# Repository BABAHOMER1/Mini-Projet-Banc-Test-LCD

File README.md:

# Banc d'essais pour écran LCD

## Présentation du projet

Ce projet a pour objectif de réaliser un banc d'essais permettant de tester des écrans LCD.

Les écrans proviennent d'un lot donné à l'établissement et leur fonctionnement n'est pas garanti.
Le banc d'essais permet donc de vérifier rapidement si un écran fonctionne correctement.

## Objectifs

- [ ] Tester l'affichage de caractères
- [ ] Permettre une connexion simple de l'écran au banc d'essais
- [ ] Réaliser une procédure de test complète et efficace
- [ ] Ajouter un potentiomètre pour le réglage du contraste
- [ ] Créer le symbole et l'empreinte de l'écran LCD
- [ ] Réaliser le schéma électronique
- [ ] Ajouter des points de test
- [ ] Réaliser le PCB

## Programmation

- [ ] Le programme de test est développé en langage C avec SimulIDE.
- [ ] La bibliothèque LiquidCrystal est utilisée pour contrôler l'écran LCD.
- [ ] L'écran fonctionne en mode 4 bits.
- [ ] Le programme de test se lance lorsque l'on appuie sur le bouton.
  
## Procédure de test

La procédure permet de vérifier progressivement le fonctionnement de l'écran

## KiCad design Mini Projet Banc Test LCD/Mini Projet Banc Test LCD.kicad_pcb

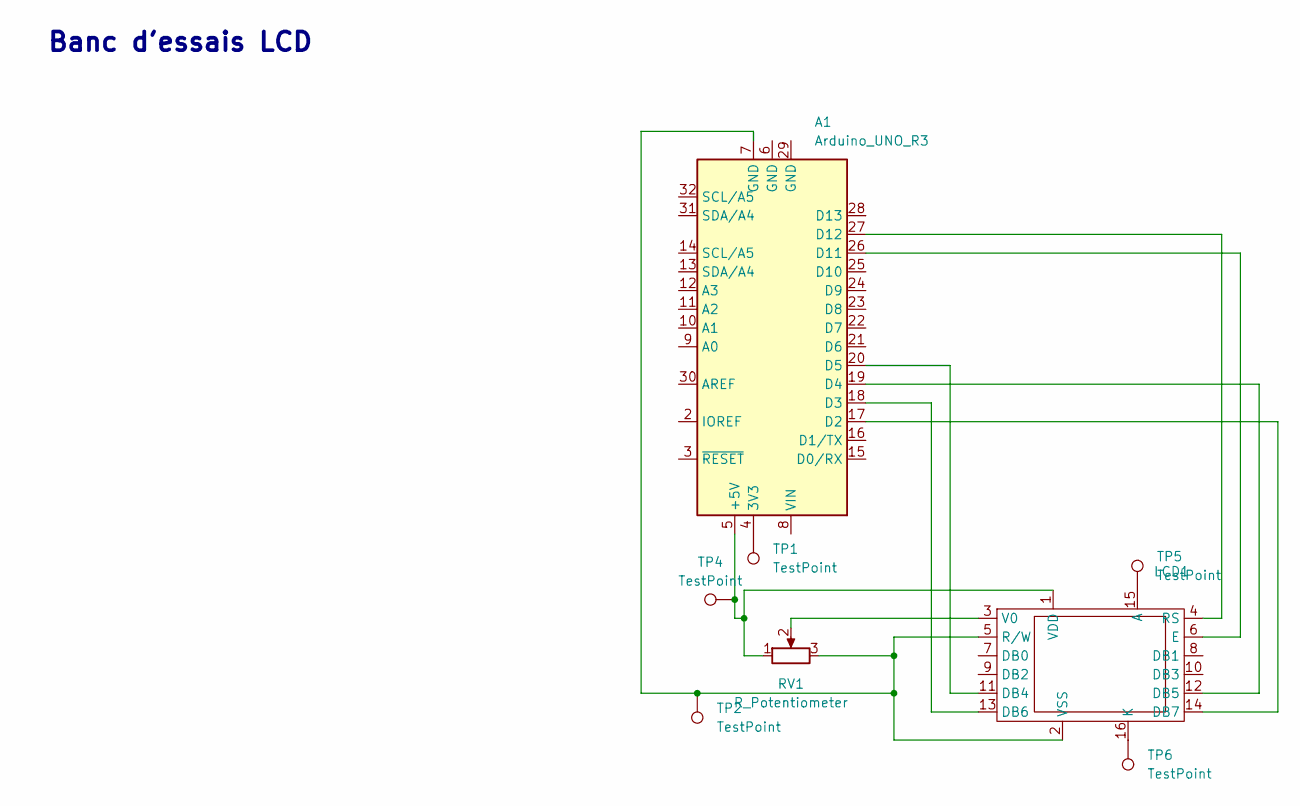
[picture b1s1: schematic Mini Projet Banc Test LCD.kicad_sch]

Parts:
A1: Arduino_UNO_R3
LCD1: LCD hitachi
RV1: R_Potentiometer; Potentiometer_ACP_CA6-H2,5_Horizontal
TP1, TP2, TP4, TP5, TP6: TestPoint; Pin_D0.7mm_L6.5mm_W1.8mm_FlatFork

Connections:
unnamed: A1.4 (3V3), TP1.1
unnamed: A1.5 (+5V), LCD1.1 (VDD), RV1.1, TP4.1
unnamed: A1.17 (D2), LCD1.14 (DB7)
unnamed: A1.18 (D3), LCD1.13 (DB6)
unnamed: A1.19 (D4), LCD1.12 (DB5)
unnamed: A1.20 (D5), LCD1.11 (DB4)
unnamed: A1.26 (D11), LCD1.6 (E)
unnamed: A1.27 (D12), LCD1.4 (RS)
unnamed: LCD1.15 (A), TP5.1
unnamed: LCD1.16 (K), TP6.1
unnamed: A1.7 (GND), LCD1.2 (VSS), LCD1.5 (R/W), RV1.3, TP2.1
unnamed: LCD1.3 (V0), RV1.2

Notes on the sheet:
Banc d'essais LCD

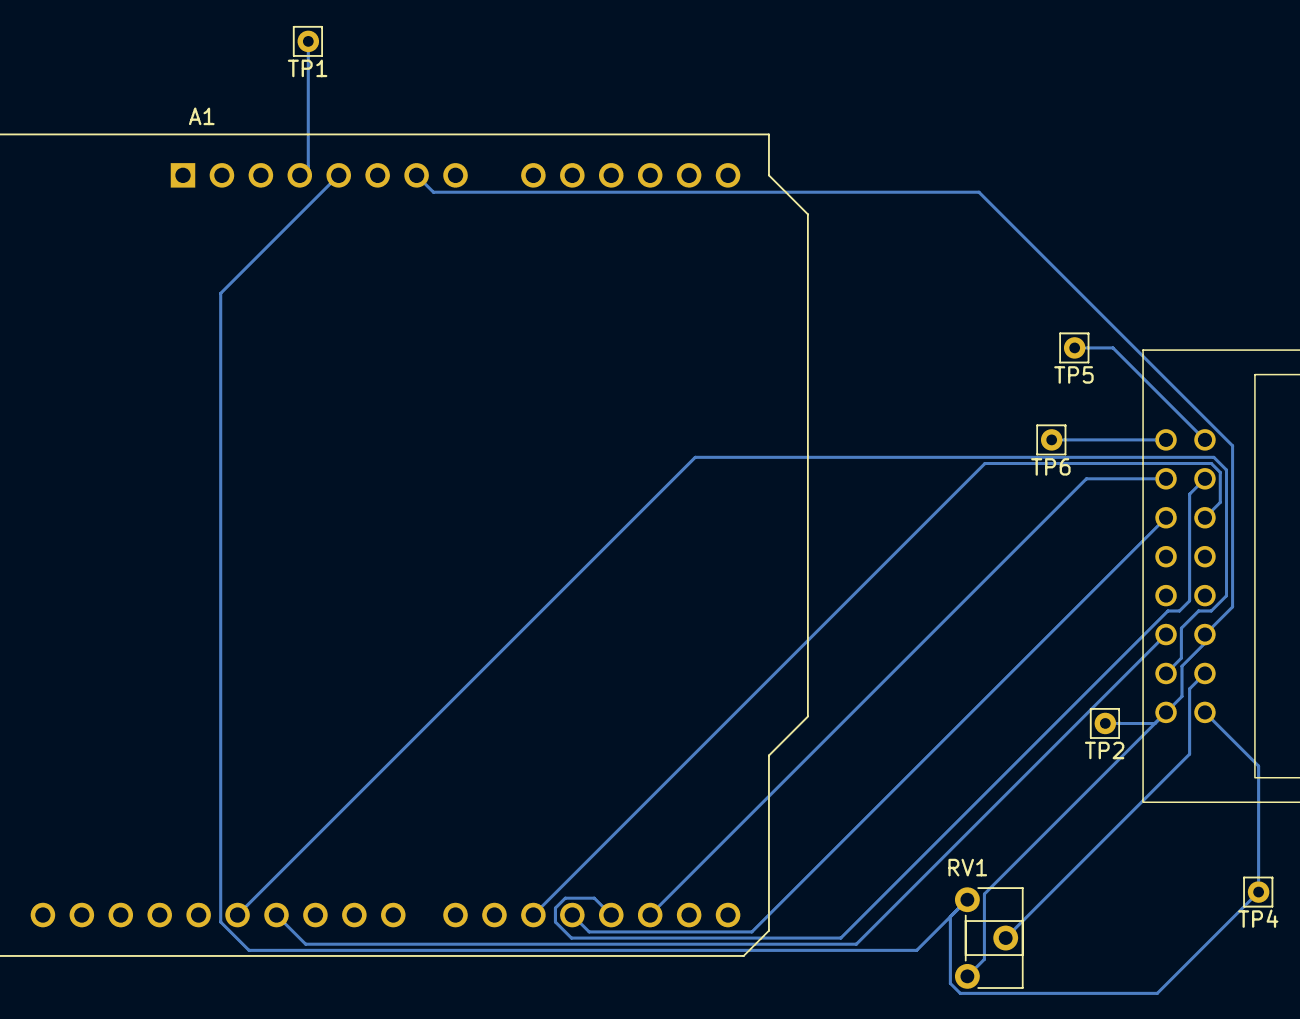
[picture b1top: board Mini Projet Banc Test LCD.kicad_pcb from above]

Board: 2 copper layers, 8 parts (0 on the bottom side), 12 nets.
